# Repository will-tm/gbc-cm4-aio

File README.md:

# GBC CM4 AIO

## Description
 
This project is a drop-in replacement board that fits and Gameboy Color shell and use the same IPS display as used in GBC kits. The goal of this project is initially fun and a bit of challenge and besides that the love for the GBC form factor and the will to leverage the wide GBC modding community to create a unique and customizable handheld device.

## Features

- GBC drop-in replacement board
- CM4 core
- 1800mAh battery
- High resolution IPS display
- PCM5102a audio DAC
- Fuel gauge battery monitoring

## Requirements to Build the GBC CM4 AIO

TBD

## Code 

TBD

## To-do

- [x] Hardware familiarization - CM$ board schematics
- [x] Design v1.0 DSI test display board for LT031MDZ4000
- [x] Order v1.0 DSI test display board for LT031MDZ4000
- [x] Design v1.0 mainboard
- [x] Order v1.0 mainboard
- [x] Bring up v1.0 mainboard
- [x] Design v1.0 DSI test display board for LS029B3SX02 (evaluation)
- [x] Order v1.0 DSI test display board for LS029B3SX02
- [x] Design v1.1 mainboard
- [x] Order v1.1 mainboard
- [ ] Bring up v1.1 mainboard
- [ ] Design flex PCB including ribbon cable to accomodate the final display
- [ ] Find a way to crop DSI panel as glass lens covers some of it
- [ ] Put together a fully functional Linux image (ongoing)
- [ ] Implement an on-screen indicator for volume, brightness control via GPIOs
- [ ] Other optimizations/improvements/bug fixes
- [ ] Create prototype showcase video
- [ ] Final GitHub open source release & announcement!

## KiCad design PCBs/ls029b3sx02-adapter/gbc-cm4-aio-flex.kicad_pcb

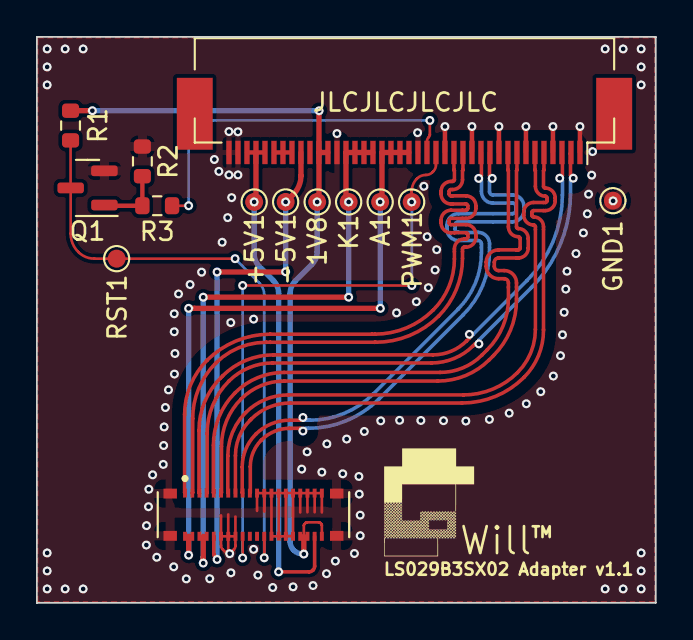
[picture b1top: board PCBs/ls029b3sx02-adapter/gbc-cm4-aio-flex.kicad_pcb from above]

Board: 2 copper layers, 34.4 x 31.4 mm, 14 parts (0 on the bottom side), 20 nets.

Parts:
1V8: TestPoint; TestPoint_Pad_D1.0mm
+5V1: TestPoint; TestPoint_Pad_D1.0mm
-5V1: TestPoint; TestPoint_Pad_D1.0mm
A1: TestPoint; TestPoint_Pad_D1.0mm
GND1: TestPoint; TestPoint_Pad_D1.0mm
J2: WP7B-S040VA1-R6000; JAE_WP7B-S040VA1-R6000
J3: Conn_01x40; Hirose_FH12-40S-0.5SH_1x40-1MP_P0.50mm_Horizontal
K1: TestPoint; TestPoint_Pad_D1.0mm
PWM1: TestPoint; TestPoint_Pad_D1.0mm
Q1: BC847; SOT-23
R1, R2: 10k; R_0603_1608Metric
R3: 1k; R_0603_1608Metric
RST1: TestPoint; TestPoint_Pad_D1.0mm

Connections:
+1V8: 1V8.1, J2.21, J2.23, J2.24, J3.29, J3.30, R1.2
+5V: +5V1.1, J2.22, J3.36, J3.37, J3.38
-5V: -5V1.1, J2.36, J3.32
/CLK_N: J2.5, J3.9
/CLK_P: J2.6, J3.8
/D0_N: J2.3, J3.3
/D0_P: J2.4, J3.2
/D1_N: J2.7, J3.6
/D1_P: J2.8, J3.5
/D2_N: J2.9, J3.12
/D2_P: J2.10, J3.11
/D3_N: J2.1, J3.15
/D3_P: J2.2, J3.14
/LCD_A: A1.1, J2.39, J2.40, J3.20, J3.21, J3.22, J3.23
/LCD_K: J2.37, J2.38, J3.24, J3.25, J3.26, J3.27, K1.1
/PWM: J2.32, J3.17, PWM1.1
/RESET: J2.29, Q1.3 (C), R1.1, RST1.1
GND: GND1.1, J2.11, J2.12, J2.13, J2.14, J2.15, J2.16, J2.17, J2.18, J2.19, J2.20, J2.25, J2.26, J2.27, J2.28, J2.33, J2.34, J2.35, J2.S1 (SHIELD), J2.S2 (SHIELD), J2.S3 (SHIELD), J2.S4 (SHIELD), J3.1, J3.7, J3.10, J3.13, J3.16, J3.19, J3.28, J3.39, J3.40, Q1.2 (E), R2.1
unnamed: J3.18, R3.1
unnamed: Q1.1 (B), R2.2, R3.2

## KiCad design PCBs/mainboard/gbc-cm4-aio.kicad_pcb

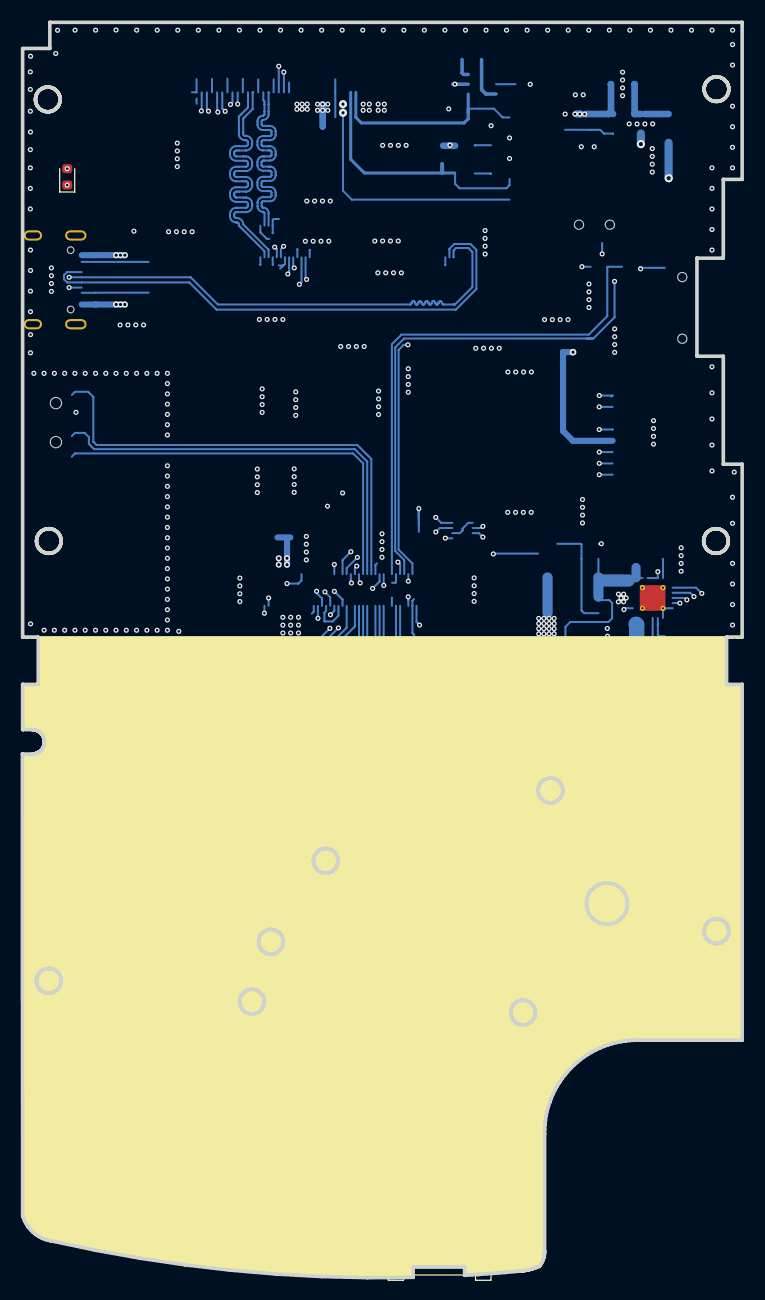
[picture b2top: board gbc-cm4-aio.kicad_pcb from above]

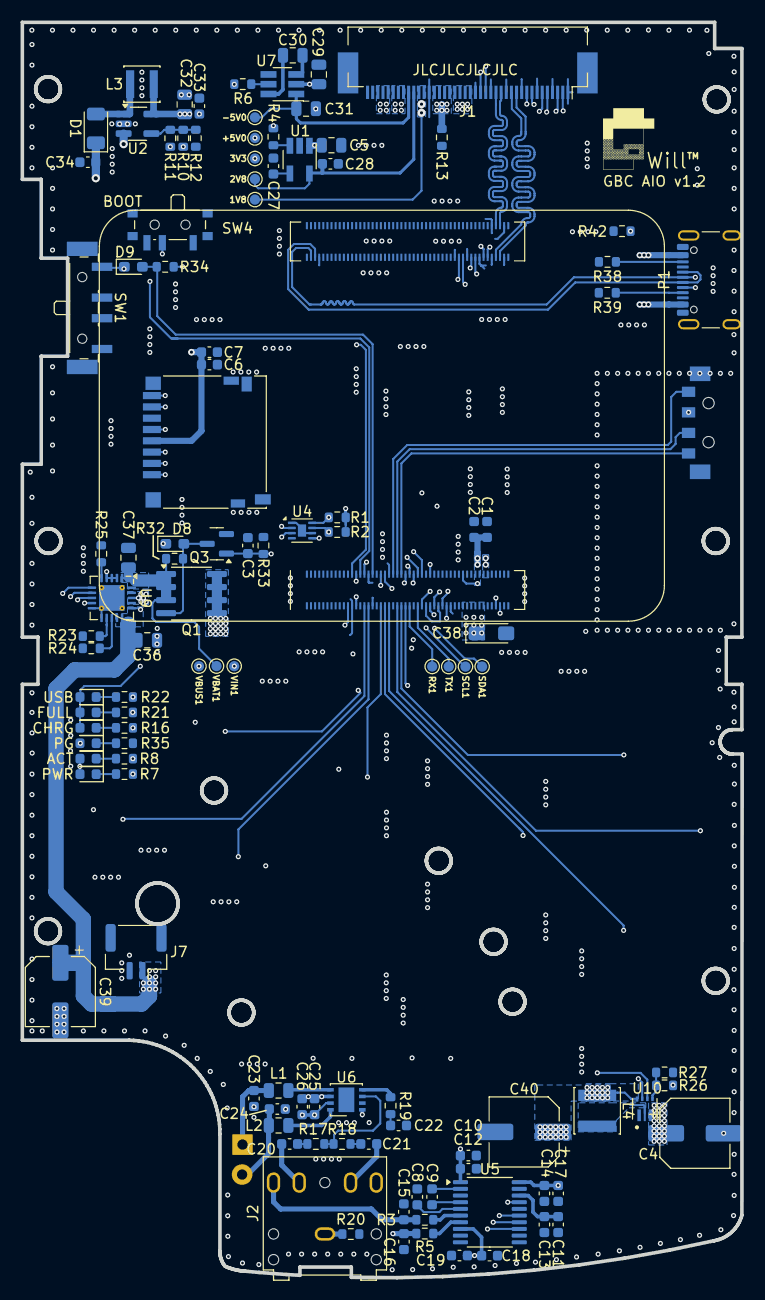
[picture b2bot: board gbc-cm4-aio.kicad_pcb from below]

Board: 4 copper layers, 70.1 x 122.2 mm, 118 parts (114 on the bottom side), 105 nets.

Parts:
1V8, 2V8, 3V3: TestPoint; TestPoint_Pad_D1.0mm
+5V0: TestPoint; TestPoint_Pad_D1.0mm
-5V0: TestPoint; TestPoint_Pad_D1.0mm
C1, C6, C10, C11, C14, C18, C25: 10uF; C_0603_1608Metric
C2, C7, C12, C13, C17, C19, C26: 0.1uF; C_0603_1608Metric
C3: 1nF; C_0603_1608Metric
C4, C39, C40: 865080443007; CP_Elec_6.3x5.4
C5, C29, C30, C31, C32: 10uF; C_0805_2012Metric
C8, C9: 2.2uF; C_0603_1608Metric
C15, C16: 2.2nF; C_0603_1608Metric
C20, C21, C22, C23, C24, C27: 10nF; C_0603_1608Metric
C28, C33, C34: 1uF; C_0603_1608Metric
C36, C37: 10uf; C_0805_2012Metric
C38: CP_EIA-3216-18_Kemet-A_Pad1.58x1.35mm_HandSolder
D1: D_Schottky; D_1206_3216Metric
D3, D4, D7: LED; LED_0603_1608Metric
D5: PWR; LED_0603_1608Metric
D6: ACT; LED_0603_1608Metric
D8, D9: D_Schottky; D_0603_1608Metric_Pad1.05x0.95mm_HandSolder
D10, D11: APA2107SECK; LED_0603_1608Metric
J1: Conn_01x40; Hirose_FH12-40S-0.5SH_1x40-1MP_P0.50mm_Horizontal
J2: AudioJack2_Ground_Switch; PJ307_jack
J4: DM3D-SF; microSD_HC_Hirose_DM3D-SF
J6: Conn_01x11; gbc_buttons
J7: Conn_01x02; JST_GH_SM02B-GHS-TB_1x02-1MP_P1.25mm_Horizontal
L1, L2: 300mR; C_0805_2012Metric
L3: 6.8uH; L_Changjiang_FNR3015S
L4: 1uH; L_Changjiang_FNR4020S
Module1: ComputeModule4-CM4; Raspberry-Pi-4-Compute-Module
P1: USB_C_Plug_USB2.0; USB_C_Receptacle_GCT_USB4105-xx-A_16P_TopMnt_Horizontal
Q1: AO4407C; SOIC-8_3.9x4.9mm_P1.27mm
Q3: 2N7002E; SOT-23
R1, R2: 1.8K; R_0603_1608Metric
R3, R5: 470R; R_0603_1608Metric
R4, R6, R10, R11, R12: 10k; R_0603_1608Metric
R7, R8, R16, R21, R22, R24, R35, R42: 1K; R_0603_1608Metric
R13: 2R; R_0603_1608Metric
R17, R18, R19: 150R; R_0603_1608Metric
R20: 6R8; R_0603_1608Metric
R23, R27: 100K; R_0603_1608Metric
R25, R34: 10K; R_0603_1608Metric
R26: 732K; R_0603_1608Metric
R32, R33: 1M; R_0603_1608Metric
R38, R39: 5.1K; R_0603_1608Metric
RX1: RX; TestPoint_Pad_D1.0mm
SCL1: SCL; TestPoint_Pad_D1.0mm
SDA1: SDA; TestPoint_Pad_D1.0mm
SPK+1: TestPoint; TestPoint_THTPad_2.5x2.5mm_Drill1.2mm
SPK-1: TestPoint; TestPoint_THTPad_D2.5mm_Drill1.2mm
SW1: SW_Push; SW_SP3T_PCM13
SW3: SW_Push_Dual_x2; SLLB510100
SW4: SW_SPDT; SW_SPDT_PCM12
TX1: TX; TestPoint_Pad_D1.0mm
U1: SGM2019-2.8YN5G/TR; SOT-23-5_HandSoldering
U2: FAN5333B; SOT-23-5_HandSoldering
U4: MAX17048G; TDFN-8-1EP_2x2mm_P0.5mm_EP0.8x1.2mm
U5: PCM5102; TSSOP-20_4.4x6.5mm_P0.65mm
U6: PAM8302AAY; DFN-8-1EP_3x3mm_P0.65mm_EP1.55x2.4mm
U7: SGM3204YN6G/TR; SOT-23-6_Handsoldering
U9: MCP73871-2CAI_ML; QFN-20-1EP_4x4mm_P0.5mm_EP2.5x2.5mm_ThermalVias
U10: TPS61022RWUR; CONV_TPS61022RWUR
VBAT1: VBAT; TestPoint_Pad_D1.0mm
VBUS1: VBUS; TestPoint_Pad_D1.0mm
VIN1: VIN; TestPoint_Pad_D1.0mm

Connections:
+1V8: 1V8.1, J1.29, J1.30, Module1.88 (+1.8v_(Output)), Module1.90 (+1.8v_(Output))
+2V8: 2V8.1, C28.1, J1.31, U1.5 (OUT)
+3V3: 3V3.1, C1.1, C2.1, C5.1, C6.1, C7.1, C10.1, C12.1, C14.1, C17.1, C18.1, C19.1, C32.1, C33.1, D5.2 (A), D6.2 (A), D11.2 (A), J1.33, J1.34, J1.35, J4.4 (VDD), L3.1, Module1.78 (GPIO_VREF(1.8v/3.3v_Input)), Module1.84 (+3.3v_(Output)), Module1.86 (+3.3v_(Output)), R1.1, R2.1, R4.1, R34.2, U1.1 (IN), U2.5 (VIN), U4.3 (VDD), U5.1 (CPVDD), U5.8 (AVDD), U5.17 (XSMT), U5.20 (DVDD)
+5V: +5V0.1, C4.1, C25.1, C26.1, C29.1, C38.1, D10.2 (A), J1.36, J1.37, J1.38, Module1.77 (+5v_(Input)), Module1.79 (+5v_(Input)), Module1.81 (+5v_(Input)), Module1.83 (+5v_(Input)), Module1.85 (+5v_(Input)), Module1.87 (+5v_(Input)), R6.1, R26.1, U6.1 (~SD), U6.6 (VDD), U7.2 (IN), U10.3 (VOUT)
+BATT: C36.2, C39.1, J7.1, U4.2 (CELL), U9.14 (VBAT), U9.15 (VBAT), U9.16 (VBAT_SENSE)
-5V: -5V0.1, C31.1, J1.32, U7.1 (OUT)
/ACT_LED: Module1.21 (PI_nLED_Activity), R8.2
/ALERT: Module1.30 (GPIO6), U4.5 (ALRT)
/AMP_L: C20.1, J2.TN
/AMP_R: C21.1, J2.RN
/AUDIO_L: C15.2, J2.T, R3.1
/AUDIO_R: C16.1, J2.R, R5.1
/BL_PWM: Module1.28 (GPIO13), R11.1
/BTN_A: J6.6, Module1.29 (GPIO16)
/BTN_B: J6.5, Module1.31 (GPIO12)
/BTN_BOTTOM: J6.3, Module1.41 (GPIO25)
/BTN_LEFT: J6.4, Module1.45 (GPIO24)
/BTN_RIGHT: J6.2, Module1.39 (GPIO8)
/BTN_SELECT: J6.8, Module1.54 (GPIO4)
/BTN_START: J6.7, Module1.50 (GPIO17)
/BTN_UP: J6.1, Module1.47 (GPIO23)
/BTN_X: J6.10, Module1.40 (GPIO9)
/BTN_Y: J6.9, Module1.37 (GPIO7)
/DSI1_BL_A: C34.2, D1.1 (K), J1.20, J1.21, J1.22, J1.23
/DSI1_BL_K: J1.24, J1.25, J1.26, J1.27, R13.2, U2.3 (FB)
/DSI1_CLK_N: J1.9, Module1.187 (DSI1_C_N)
/DSI1_CLK_P: J1.8, Module1.189 (DSI1_C_P)
/DSI1_D0_N: J1.3, Module1.175 (DSI1_D0_N)
/DSI1_D0_P: J1.2, Module1.177 (DSI1_D0_P)
/DSI1_D1_N: J1.6, Module1.181 (DSI1_D1_N)
/DSI1_D1_P: J1.5, Module1.183 (DSI1_D1_P)
/DSI1_D2_N: J1.12, Module1.193 (DSI1_D2_N)
/DSI1_D2_P: J1.11, Module1.195 (DSI1_D2_P)
/DSI1_D3_N: J1.15, Module1.194 (DSI1_D3_N)
/DSI1_D3_P: J1.14, Module1.196 (DSI1_D3_P)
/DSI1_PWM: J1.17, R10.1
/DSI1_RESET: J1.18, Module1.24 (GPIO26)
/IP0: P1.A5 (CC1), R39.1
/IP1: P1.B5 (CC2), R38.1
/NAV_CLICK: Module1.46 (GPIO22), SW3.T1 (C)
/NAV_DOWN: Module1.48 (GPIO27), SW3.2 (D)
/NAV_UP: Module1.44 (GPIO10), SW3.1 (C)
/PCM_CLK: Module1.49 (GPIO18), U5.13 (BCK)
/PCM_DOUT: Module1.25 (GPIO21), U5.14 (DIN)
/PCM_FS: Module1.26 (GPIO19), U5.15 (LRCK)
/PWR_LED: Module1.95 (nPI_LED_PWR), R7.2
/PWR_ON: C3.2, Module1.38 (GPIO11), Q3.1 (G), R33.2
/PWR_SW: D9.2 (A), Module1.34 (GPIO5), R34.1
/RPI_BOOT: Module1.93 (nRPIBOOT), SW4.2 (B)
/RXD0: Module1.51 (GPIO15), RX1.1
/SCL1: Module1.56 (GPIO3), R2.2, SCL1.1, U4.7 (SCL)
/SDA1: Module1.58 (GPIO2), R1.2, SDA1.1, U4.8 (SDA)
/SD_CLK: J4.5 (CLK), Module1.57 (SD_CLK)
/SD_CMD: J4.3 (CMD), Module1.62 (SD_CMD)
/SD_DAT0: J4.7 (DAT0), Module1.63 (SD_DAT0)
/SD_DAT1: J4.8 (DAT1), Module1.67 (SD_DAT1)
/SD_DAT2: J4.1 (DAT2), Module1.69 (SD_DAT2)
/SD_DAT3: J4.2 (DAT3/CD), Module1.61 (SD_DAT3)
/SW: L4.2, U10.2 (SW)
/TXD0: Module1.55 (GPIO14), TX1.1
/USB_N: Module1.103 (USB2_N), P1.A7 (D-), P1.B7 (D-)
/USB_P: Module1.105 (USB2_P), P1.A6 (D+), P1.B6 (D+)
/VBAT: C37.2, Q1.1 (S), Q1.2 (S), Q1.3 (S), R32.1, U9.1 (OUT), U9.20 (OUT), VBAT1.1
/VIN: C40.1, L4.1, Q1.5 (D), Q1.6 (D), Q1.7 (D), Q1.8 (D), U10.5 (EN), U10.7 (VIN), VIN1.1
GND: C1.2, C2.2, C3.1, C4.2, C5.2, C6.2, C7.2, C8.2, C10.2, C11.2, C12.2, C13.2, C14.2, C15.1, C16.2, C17.2, C18.2, C19.2, C22.1, C23.2, C24.1, C25.2, C26.2, C27.2, C28.2, C29.2, C31.2, C32.2, C33.2, C34.1, C36.1, C37.1, C38.2, C39.2, C40.2, J1.1, J1.4, J1.7, J1.10, J1.13, J1.16, J1.19, J1.28, J1.39, J1.40, J4.6 (VSS), J4.11 (SHIELD), J6.11, J7.2, Module1.1 (GND), Module1.2 (GND), Module1.7 (GND), Module1.8 (GND), Module1.13 (GND), Module1.14 (GND), Module1.22 (GND), Module1.23 (GND), Module1.32 (GND), Module1.33 (GND), Module1.42 (GND), Module1.43 (GND), Module1.52 (GND), Module1.53 (GND), Module1.59 (GND), Module1.60 (GND), Module1.65 (GND), Module1.66 (GND), Module1.71 (GND), Module1.74 (GND), Module1.98 (GND), Module1.107 (GND), Module1.108 (GND), Module1.113 (GND), Module1.114 (GND), Module1.119 (GND), Module1.120 (GND), Module1.125 (GND), Module1.126 (GND), Module1.131 (GND), Module1.132 (GND), Module1.137 (GND), Module1.138 (GND), Module1.144 (GND), Module1.150 (GND), Module1.155 (GND), Module1.156 (GND), Module1.161 (GND), Module1.162 (GND), Module1.167 (GND), Module1.168 (GND), Module1.173 (GND), Module1.174 (GND), Module1.179 (GND), Module1.180 (GND), Module1.185 (GND), Module1.186 (GND), Module1.191 (GND), Module1.192 (GND), Module1.197 (GND), Module1.198 (GND), P1.A1 (GND), P1.A12 (GND), P1.B1 (GND), P1.B12 (GND), P1.S1 (SHIELD), Q3.2 (S), R12.1, R13.1, R20.2, R23.2, R24.2, R25.2, R27.2, R33.1, R35.2, R38.2, R39.2, R42.2, SW1.2, SW3.C1 (D), SW4.3 (C), U1.2 (GND), U2.2 (GND), U4.1 (CTG), U4.4 (GND), U4.6 (QSTRT), U4.9 (GND), U5.3 (CPGND), U5.9 (AGND), U5.10 (DEMP), U5.11 (FLT), U5.16 (FMT), U5.19 (DGND), U6.7 (GND), U7.4 (GND), U9.10 (VSS), U9.11 (VSS), U9.21 (VSS), U10.1 (GND), U10.6 (MODE)
GNDA: J2.S, R20.1
unnamed: C20.2, R17.2
unnamed: C21.2, R18.2
unnamed: C22.2, R19.2
unnamed: C23.1, L1.1, SPK+1.1
unnamed: C24.2, L2.1, SPK-1.1
unnamed: D1.2 (A), L3.2, U2.1 (SW)
unnamed: D3.1 (K), R16.2
unnamed: D4.1 (K), R21.2
unnamed: D5.1 (K), R7.1
unnamed: D6.1 (K), R8.1
unnamed: D7.1 (K), R22.2
unnamed: D8.2 (A), Q1.4 (G), Q3.3 (D), R32.2
unnamed: D8.1 (K), D9.1 (K), SW1.1
unnamed: D10.1 (K), R35.1
unnamed: D11.1 (K), R42.1
unnamed: C27.1, U1.4 (BP)
unnamed: R4.2, U1.3 (EN)
unnamed: R10.2, R11.2, R12.2, U2.4 (SHDN)
unnamed: C9.2, U5.4 (CAPM)
unnamed: C9.1, U5.2 (CAPP)
unnamed: C11.1, C13.1, U5.18 (LDOO)
unnamed: R3.2, U5.6 (OUTL)
unnamed: R5.2, U5.7 (OUTR)
unnamed: C8.1, U5.5 (VNEG)
unnamed: R17.1, R18.1, U6.3 (IN+)
unnamed: R19.1, U6.4 (IN-)
unnamed: L1.2, U6.5 (OUT+)
unnamed: L2.2, U6.8 (OUT-)
unnamed: C30.2, U7.6 (CFLY+)
unnamed: C30.1, U7.3 (CFLY-)
unnamed: R6.2, U7.5 (EN)
unnamed: R24.1, U9.13 (PROG1)
unnamed: R23.1, U9.12 (PROG3)
unnamed: R22.1, U9.8 (STAT1/~LBO)
unnamed: R21.1, U9.7 (STAT2)
unnamed: R25.1, U9.5 (THERM)
unnamed: R16.1, U9.6 (~PG)
unnamed: R26.2, R27.1, U10.4 (FB)
VBUS: D3.2 (A), D4.2 (A), D7.2 (A), P1.A4 (VBUS), P1.A9 (VBUS), P1.B4 (VBUS), P1.B9 (VBUS), U9.2 (VPCC), U9.3 (SEL), U9.4 (PROG2), U9.9 (~TE), U9.17 (CE), U9.18 (IN), U9.19 (IN), VBUS1.1

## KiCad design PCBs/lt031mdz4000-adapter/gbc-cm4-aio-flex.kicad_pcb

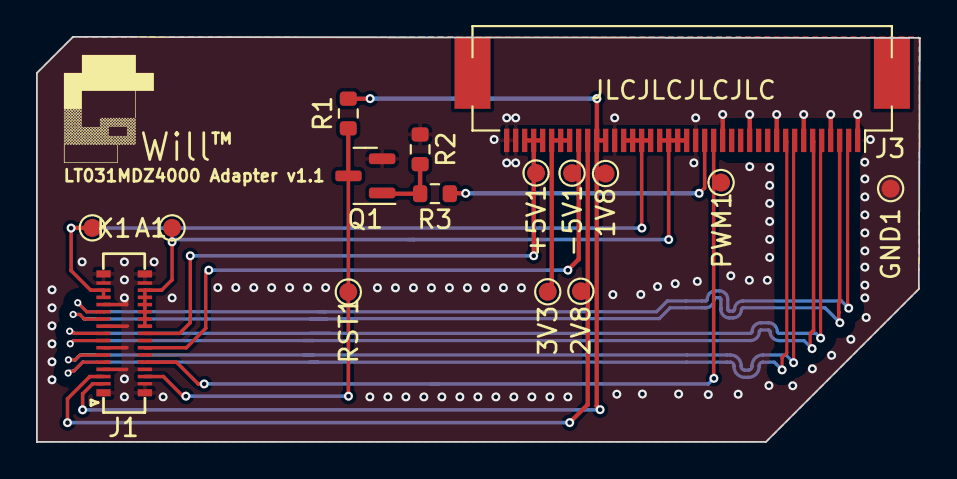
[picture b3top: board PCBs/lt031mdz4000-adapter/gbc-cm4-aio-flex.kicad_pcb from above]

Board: 2 copper layers, 49.1 x 22.5 mm, 16 parts (0 on the bottom side), 18 nets.

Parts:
1V8, 2V8, 3V3: TestPoint; TestPoint_Pad_D1.0mm
+5V1: TestPoint; TestPoint_Pad_D1.0mm
-5V1: TestPoint; TestPoint_Pad_D1.0mm
A1: TestPoint; TestPoint_Pad_D1.0mm
GND1: TestPoint; TestPoint_Pad_D1.0mm
J1: Conn_02x15_Odd_Even; BM14B(0.8)-30DS-0.4V(52)
J3: Conn_01x40; Hirose_FH12-40S-0.5SH_1x40-1MP_P0.50mm_Horizontal
K1: TestPoint; TestPoint_Pad_D1.0mm
PWM1: TestPoint; TestPoint_Pad_D1.0mm
Q1: BC847; SOT-23
R1, R2: 10k; R_0603_1608Metric
R3: 1k; R_0603_1608Metric
RST1: TestPoint; TestPoint_Pad_D1.0mm

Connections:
+1V8: 1V8.1, J1.1, J3.29, J3.30, R1.2
+2V8: 2V8.1, J1.3, J3.31
+3.3V: 3V3.1, J3.33, J3.34, J3.35
+5V: +5V1.1, J1.16, J3.36, J3.37, J3.38
-5V: -5V1.1, J1.12, J3.32
/CLK_N: J1.7, J3.9
/CLK_P: J1.9, J3.8
/D0_N: J1.19, J3.3
/D0_P: J1.21, J3.2
/D1_N: J1.13, J3.6
/D1_P: J1.15, J3.5
/LCD_A: A1.1, J1.18, J1.20, J1.22, J1.24, J1.26, J1.28, J3.20, J3.21, J3.22, J3.23
/LCD_K: J1.25, J1.27, J3.24, J3.25, J3.26, J3.27, K1.1
/PWM: J1.8, J3.17, PWM1.1
/RESET: J1.4, Q1.3 (C), R1.1, RST1.1
GND: GND1.1, J1.2, J1.5, J1.6, J1.10, J1.11, J1.14, J1.17, J1.23, J1.29, J1.30, J1.MP, J3.1, J3.7, J3.10, J3.13, J3.16, J3.19, J3.28, J3.39, J3.40, Q1.2 (E), R2.1
unnamed: J3.18, R3.1
unnamed: Q1.1 (B), R2.2, R3.2

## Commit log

2024-01-27 minor tweaks
2024-02-22 clearance adjustment
2024-02-24 MAX17048 package fix, added front power led, minor tweaks
2024-02-25 cosmetics
2024-03-02 remove global_en, move boot to more accessible location
2024-03-02 usbc positioning improvement
2024-03-02 volume wheel positioning improvement
2024-03-02 led positioning improvement
2024-03-03 move x button to avoid potential conflict with i2s
2024-03-03 display connector positioning improvement, display lines delay matching
2024-03-04 clean small drill sizes
2024-03-05 Backlight driver improvement
2024-03-05 battery connector positioning improvement
2024-03-05 relayout power supply and audio
2024-03-06 cosmetics and optimizations
2024-03-06 added battery gauge alert
2024-03-06 added adapter boards
2024-03-07 Add license
2024-03-07 Remove ignored files
2024-03-12 revise sd card and lcd driver placement
2024-03-12 bump version number
2024-03-13 led backlight
2024-03-17 move i2c bus to i2c1
2024-03-17 bring back leds to back
2024-03-17 revise inductors packages
2024-03-17 minor optimizations
2024-03-22 fix ls029b3sx02-adapter connector package
2024-03-22 mainboard differential pairs layout optimization
2024-03-25 mainboard placement optimization
2024-03-26 added tactile switches
